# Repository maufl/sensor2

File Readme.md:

# A ESP based sensor platform
This is a learning project for me. The goal is to build sensors (and maybe eventually actors) using ESP32 micro-controllers that can run on battery for a long time (a year and more).
I started it to learn PCB design and embedded programming.

## Climate sensor
The hardware design for the climate sensor does work now the way I hoped. 
Most of all this means that the linear voltage regulator provides enough power even when sending data over WiFi or BLE 
and that I can put the ESP into deep sleep and the whole board will only consume around 11µA.

Software wise I do have a firmware written in Rust that periodically sends measurements via BLE using the [BTHome](https://bthome.io/) standard and goes into deep sleep during the rest of the time.

Using an small LiPo battery with 700mAh it should last at least a year.

There is an (even more) experimental feature of doing the measurements using the low power core that is not working yet. 
The idea would be to measure with a higher frequency than send measurements with a lower frequency, thus saving power.

## License
All hardware is licensed under CERN OHL S 2.0 and all software is licensed under GNU GPLv3.

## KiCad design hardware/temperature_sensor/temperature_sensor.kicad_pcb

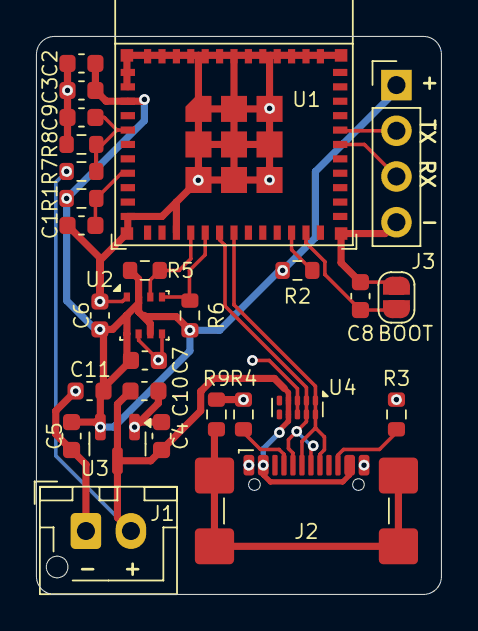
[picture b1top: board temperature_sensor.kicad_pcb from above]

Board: 2 copper layers, 22.5 x 31.0 mm, 28 parts (0 on the bottom side), 16 nets.

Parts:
BOOT: SolderJumper_2_Open; SolderJumper-2_P1.3mm_Open_RoundedPad1.0x1.5mm
C1: 1µF; C_0603_1608Metric
C2, C8, C9: 100nF; C_0603_1608Metric
C3: 10µF; C_0603_1608Metric
C4, C5: 1 µF; C_0603_1608Metric
C6, C7: 100 nF; C_0603_1608Metric
C10, C11: 47µF; C_0603_1608Metric
J1: Conn_01x02_Male; JST_XH_B2B-XH-AM_1x02_P2.50mm_Vertical
J2: USB_C_Receptacle_USB2.0_16P; USB_C_Receptacle_GCT_USB4110
J3: Conn_01x04_Socket; PinHeader_1x04_P2.54mm_Vertical
R1: 10K 1%; R_0603_1608Metric
R2: 3.3K 1%; R_0603_1608Metric
R3, R4: 5.1K; R_0603_1608Metric
R5, R6: 4.7 k; R_0603_1608Metric
R7: 4,7 M; R_0603_1608Metric
R8: 1 M; R_0603_1608Metric
R9: 1M; R_0603_1608Metric
U1: ESP32-C6-MINI-1/U; ESP32-C6-MINI-1
U2: BME280; Bosch_LGA-8_2.5x2.5mm_P0.65mm_ClockwisePinNumbering
U3: MCP1700x-330xxTT; SOT-23
U4: TPD4E02B04DQA; USON-10_2.5x1.0mm_P0.5mm

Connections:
+3.3V: C2.1, C3.1, C5.1, C6.1, C7.1, C11.1, J3.1, R1.1, R2.2, R5.1, R6.1, U1.3 (3V3), U2.2 (CSB), U2.6 (VDDIO), U2.8 (VDD), U3.2 (VO)
+BATT: C4.1, C10.1, J1.2, J2.A4 (VBUS), J2.A9 (VBUS), J2.B4 (VBUS), J2.B9 (VBUS), R7.1, U3.3 (VI), U4.4 (IO3), U4.7 (NC)
/ADC: C9.2, R7.2, R8.1, U1.5 (GPIO2/ADC1_CH2)
/BOOT_MODE: BOOT.1 (A), C8.2, U1.23 (GPIO9)
/EN: C1.2, R1.2, U1.8 (EN/CHIP_PU)
/I2C_SCL: R6.2, U1.16 (MTDO/GPIO7), U2.4 (SCK)
/I2C_SDA: R5.2, U1.15 (MTCK/GPIO6/ADC1_CH6), U2.3 (SDI)
/U0RXD: J3.3, U1.30 (U0RXD/GPIO17)
/U0TXD: J3.2, U1.31 (U0TXD/GPIO16)
/USB_D+: J2.A6 (D+), J2.B6 (D+), U1.18 (GPIO13/USB_D+), U4.1 (IO1), U4.10 (NC)
/USB_D-: J2.A7 (D-), J2.B7 (D-), U1.17 (GPIO12/USB_D-), U4.2 (IO2), U4.9 (NC)
GND: BOOT.2 (B), C1.1, C2.2, C3.2, C4.2, C5.2, C6.2, C7.2, C8.1, C9.1, C10.2, C11.2, J1.1, J2.A1 (GND), J2.A12 (GND), J2.B1 (GND), J2.B12 (GND), J3.4, R3.2, R4.2, R8.2, R9.2, U1.1 (GND), U1.2 (GND), U1.11 (GND), U1.14 (GND), U1.36 (GND), U1.37 (GND), U1.38 (GND), U1.39 (GND), U1.40 (GND), U1.41 (GND), U1.42 (GND), U1.43 (GND), U1.44 (GND), U1.45 (GND), U1.46 (GND), U1.47 (GND), U1.48 (GND), U1.49 (GND), U1.50 (GND), U1.51 (GND), U1.52 (GND), U1.53 (GND), U2.1 (GND), U2.5 (SDO), U2.7 (GND), U3.1 (GND), U4.3 (G), U4.8 (G)
unnamed: J2.A5 (CC1), R4.1
unnamed: J2.B5 (CC2), R3.1
unnamed: J2.S1 (SHIELD), R9.1
unnamed: R2.1, U1.22 (GPIO8)

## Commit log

2024-09-08 Initial commit, basic version with HP and LP core working
2024-09-29 Add code to read sensor form HP core
2024-09-29 Try updating dependencies for LP code
2024-09-29 Try debugging with probe-rs
2024-09-29 Add hardware design
2024-10-27 I don't know what happened
2024-10-27 Add LP core use as feature, reformat file
2024-10-31 Update schema and PCB, more caps, antenna hanging free
2024-11-01 Use grid override for text
2024-11-24 Update esp crate dependencies
2024-11-24 Add battery charge reading
2024-11-28 wip: Trying to make BLE work
2024-12-03 Send measurements using BLE and the BThome format
2024-12-04 Refactor, share logic between LP and HP, improve LP code
2024-12-04 Improve the battery voltage reading
2024-12-05 Increase sleep period
2024-12-05 Add license
2025-01-04 Add housing prototype
2025-01-17 Use one gitignore only
2025-01-17 Update dependencies
2025-01-17 Add Cargo lock file for shared code
